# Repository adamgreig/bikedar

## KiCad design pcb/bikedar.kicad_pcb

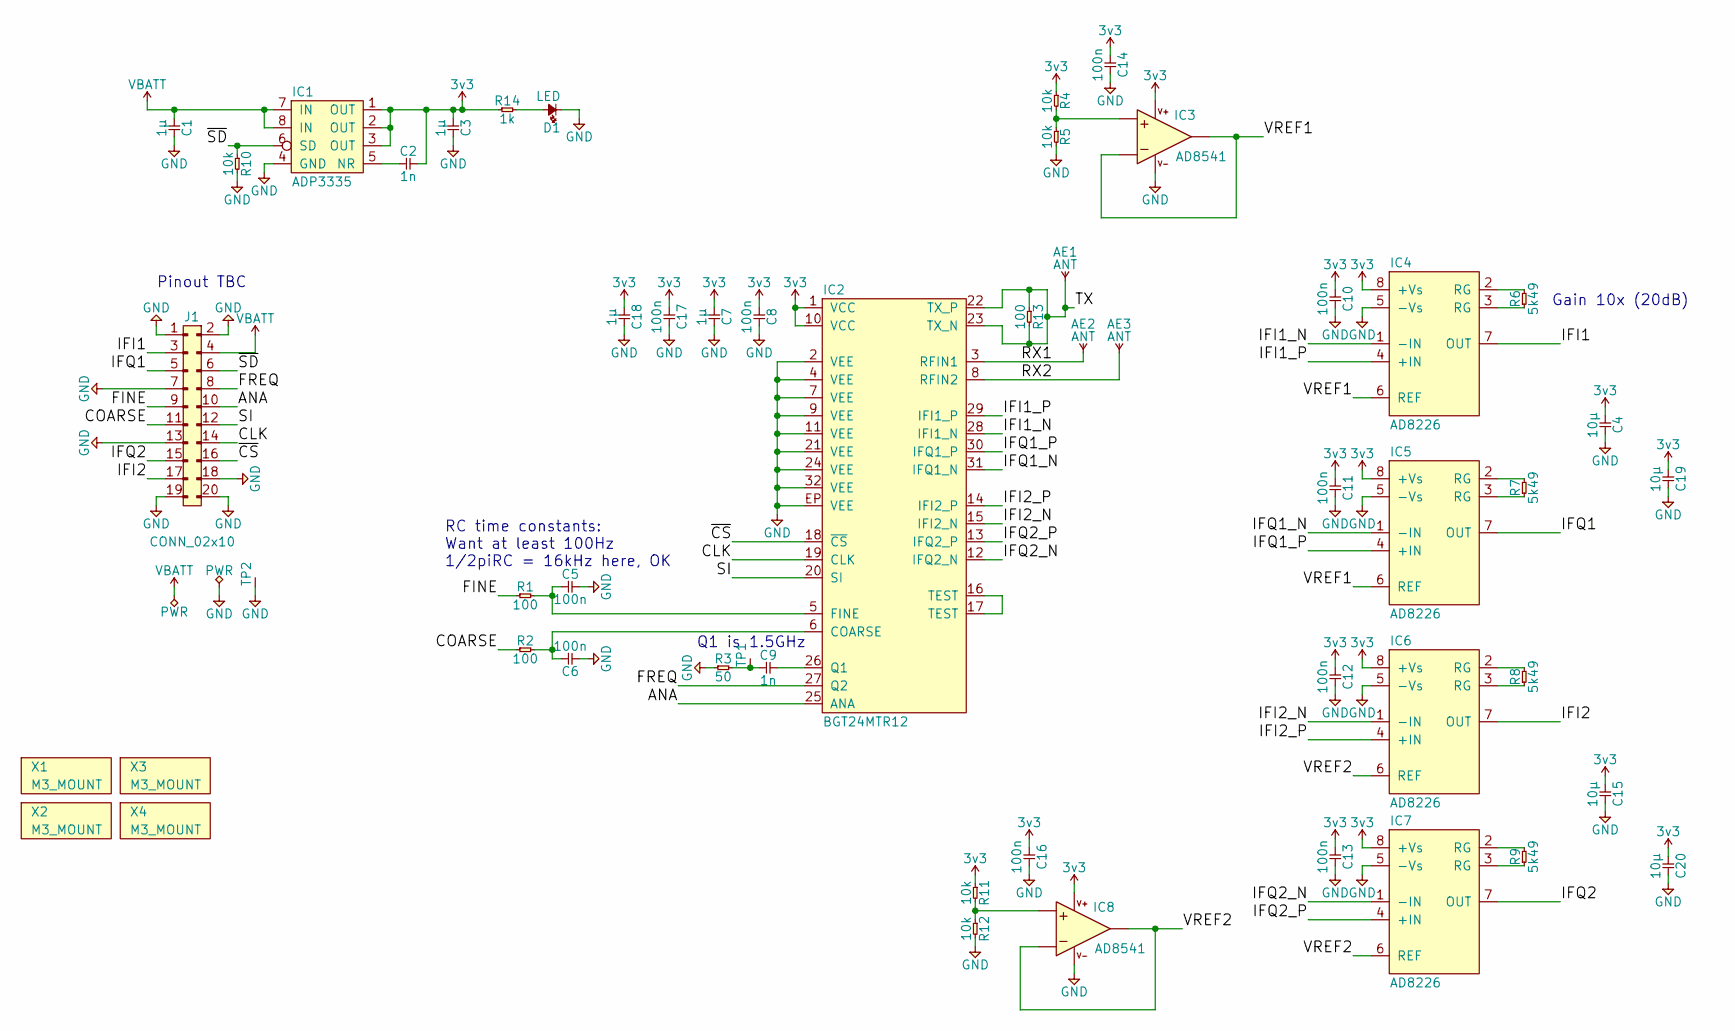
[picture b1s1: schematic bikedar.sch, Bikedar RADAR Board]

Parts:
AE1, AE2, AE3: ANT
C1, C3, C7, C18: 1µ; 0603
C2: 1n; 0603
C4, C15, C19, C20: 10µ; 0603
C5, C6: 100n; 0402
C8, C10, C11, C12, C13, C14, C16, C17: 100n; 0603
C9: 1n; 0402
D1: LED; 0603-LED
IC1: ADP3335; MSOP-8; Farnell 2067775
IC2: BGT24MTR12; QFN-32-BGT24MTR; Farnell 2710089
IC3, IC8: AD8541; SC-70-5; Farnell 1333254
IC4, IC5, IC6, IC7: AD8226; MSOP-8; Farnell 2462026
J1: CONN_02x10; DIL-254P-20
R1, R2, R13: 100; 0402
R3: 50; 0402
R4, R5, R10, R11, R12: 10k; 0603
R6, R7, R8, R9: 5k49; 0402
R14: 1k; 0603
TP1: TESTPAD
TP2: TESTPAD; SIL-254P-01
X1, X2, X3, X4: M3_MOUNT

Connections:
3v3: C2.2, C3.1, C4.1, C7.1, C8.1, C10.1, C11.1, C12.1, C13.1, C14.1, C15.1, C16.1, C17.1, C18.1, C19.1, C20.1, IC1.1 (OUT), IC1.2 (OUT), IC1.3 (OUT), IC2.1 (VCC), IC2.10 (VCC), IC3.5 (V+), IC4.8 (+Vs), IC5.8 (+Vs), IC6.8 (+Vs), IC7.8 (+Vs), IC8.5 (V+), R4.1, R11.1, R14.1
/ANA: IC2.25 (ANA), J1.10
/CLK: IC2.19 (CLK), J1.14
/COARSE: J1.11, R2.1
/FINE: J1.9, R1.1
/FREQ: IC2.27 (Q2), J1.8
/IFI1: IC4.7 (OUT), J1.3
/IFI1_N: IC2.28 (IFI1_N), IC4.1 (-IN)
/IFI1_P: IC2.29 (IFI1_P), IC4.4 (+IN)
/IFI2: IC6.7 (OUT), J1.17
/IFI2_N: IC2.15 (IFI2_N), IC6.1 (-IN)
/IFI2_P: IC2.14 (IFI2_P), IC6.4 (+IN)
/IFQ1: IC5.7 (OUT), J1.5
/IFQ1_N: IC2.31 (IFQ1_N), IC5.1 (-IN)
/IFQ1_P: IC2.30 (IFQ1_P), IC5.4 (+IN)
/IFQ2: IC7.7 (OUT), J1.15
/IFQ2_N: IC2.12 (IFQ2_N), IC7.1 (-IN)
/IFQ2_P: IC2.13 (IFQ2_P), IC7.4 (+IN)
/RX1: AE2.1, IC2.3 (RFIN1)
/RX2: AE3.1, IC2.8 (RFIN2)
/SI: IC2.20 (SI), J1.12
/TX: AE1.1, IC2.22 (TX_P), IC2.23 (TX_N), R13.1, R13.2
/VREF1: IC3.1 (OUT), IC3.4 (-), IC4.6 (REF), IC5.6 (REF)
/VREF2: IC6.6 (REF), IC7.6 (REF), IC8.1 (OUT), IC8.4 (-)
/~CS: IC2.18 (~CS), J1.16
/~SD: IC1.6 (SD), J1.6, R10.1
GND: C1.2, C3.2, C4.2, C5.2, C6.1, C7.2, C8.2, C10.2, C11.2, C12.2, C13.2, C14.2, C15.2, C16.2, C17.2, C18.2, C19.2, C20.2, D1.1, IC1.4 (GND), IC2.2 (VEE), IC2.4 (VEE), IC2.7 (VEE), IC2.9 (VEE), IC2.11 (VEE), IC2.21 (VEE), IC2.24 (VEE), IC2.32 (VEE), IC2.EP (VEE), IC3.2 (V-), IC4.5 (-Vs), IC5.5 (-Vs), IC6.5 (-Vs), IC7.5 (-Vs), IC8.2 (V-), J1.1, J1.2, J1.7, J1.13, J1.18, J1.19, J1.20, R3.1, R5.2, R10.2, R12.2, TP2.1
unnamed: C2.1, IC1.5 (NR)
unnamed: C5.1, IC2.5 (FINE), R1.2
unnamed: C6.2, IC2.6 (COARSE), R2.2
unnamed: C9.1, R3.2, TP1.1
unnamed: C9.2, IC2.26 (Q1)
unnamed: D1.2, R14.2
unnamed: IC2.16 (TEST), IC2.17 (TEST)
unnamed: IC3.3 (+), R4.2, R5.1
unnamed: IC4.2 (RG), R6.2
unnamed: IC4.3 (RG), R6.1
unnamed: IC5.2 (RG), R7.2
unnamed: IC5.3 (RG), R7.1
unnamed: IC6.2 (RG), R8.2
unnamed: IC6.3 (RG), R8.1
unnamed: IC7.2 (RG), R9.2
unnamed: IC7.3 (RG), R9.1
unnamed: IC8.3 (+), R11.2, R12.1
VBATT: C1.1, IC1.7 (IN), IC1.8 (IN), J1.4

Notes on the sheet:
Q1 is 1.5GHz
RC time constants: Want at least 100Hz 1/2piRC = 16kHz here, OK
Pinout TBC
Gain 10x (20dB)

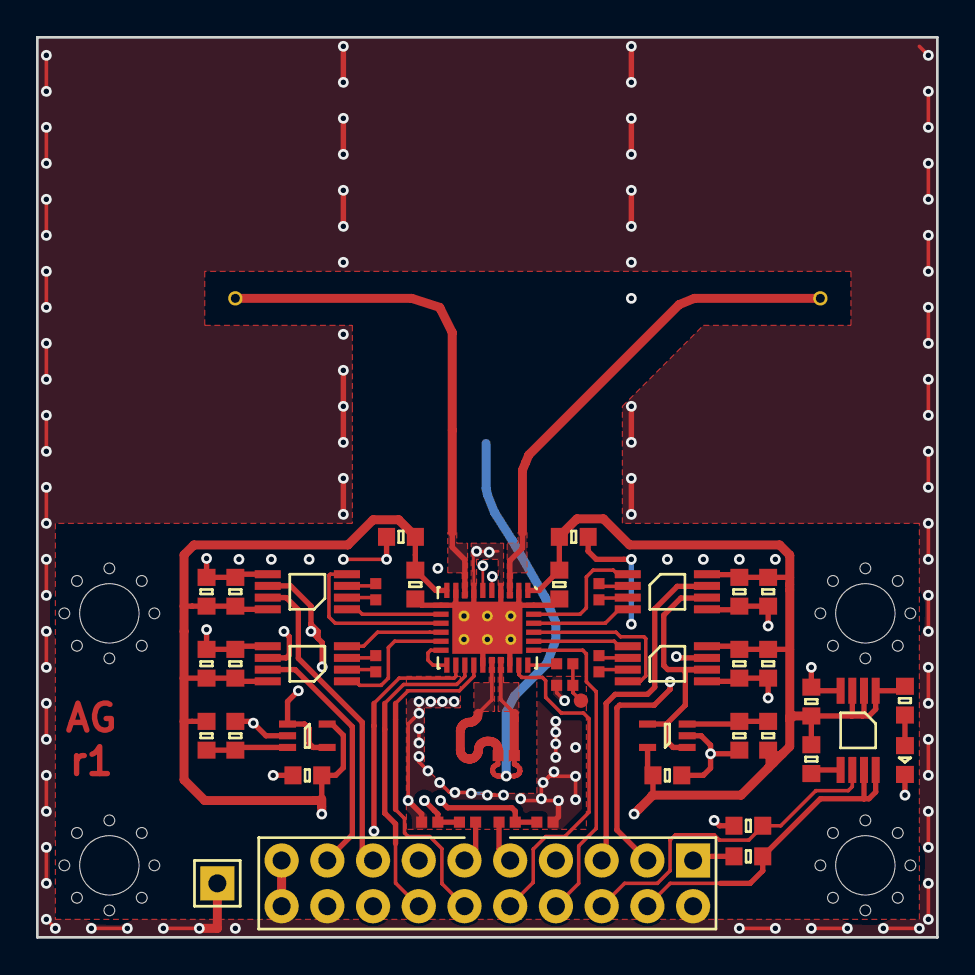
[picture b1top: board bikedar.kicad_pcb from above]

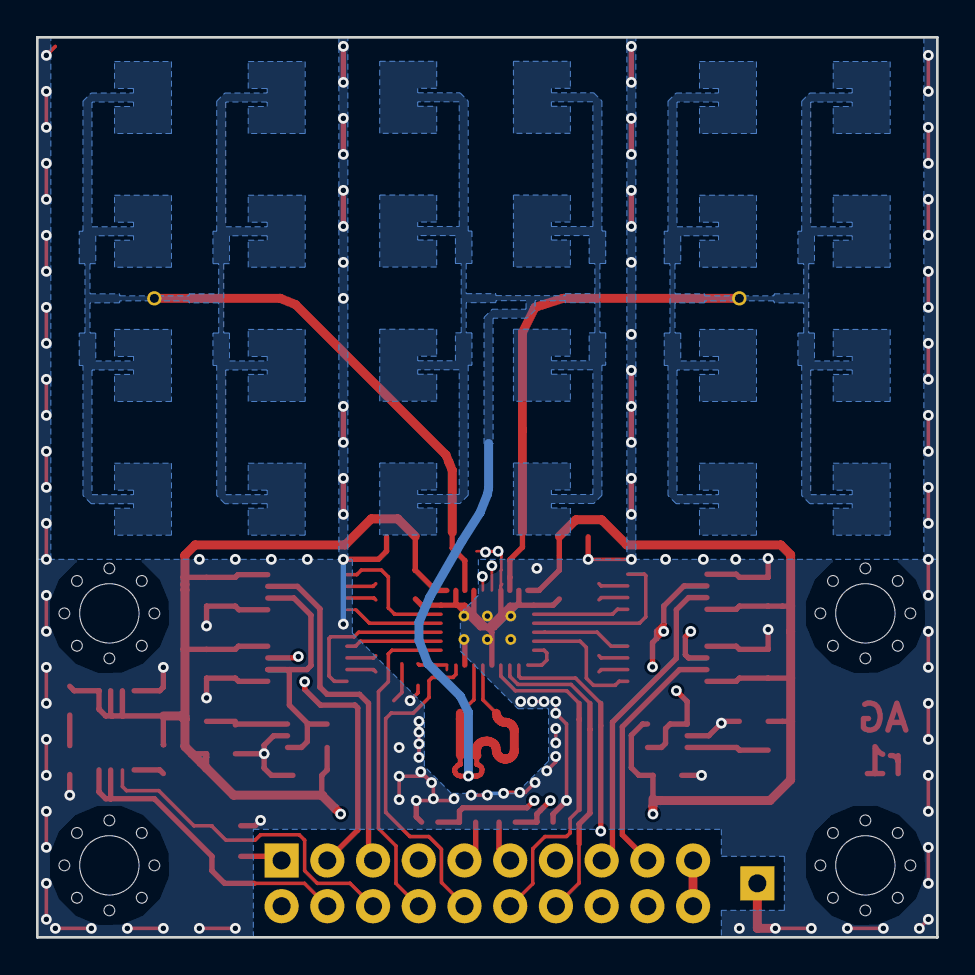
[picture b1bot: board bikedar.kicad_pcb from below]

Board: 4 copper layers, 50.0 x 50.0 mm, 52 parts (2 on the bottom side), 45 nets.

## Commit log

2017-05-16 first go at radar pcb and copy in antenna script from m3r
2017-05-16 add 3d renders of board
2017-05-16 tidy up and add lots of gnd
2017-05-16 more rf work..
2017-05-17 nicer balun
2017-05-17 further tidying
2017-05-18 first go at antenna array
2017-05-18 antennas are go
2017-05-18 final tidying. almost ready to go but vias wrong size?!
2017-05-18 r1 RFM
2017-05-18 add mouser parts to bom (parts ordered)
2017-05-30 add bom
2017-06-07 dodgy ethernet using cm-quickstart template
2017-06-07 try out smoltcp
2017-06-08 nicer eth/phy driver including better td/rd management
2017-06-09 add cache test/bench stuff
